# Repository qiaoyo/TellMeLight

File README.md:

# TellMeLight

TellMeLight is a USB-connected AI hardware design for visualizing local AI sessions as a persistent six-slot light queue.

Current milestone: local software simulation plus a Rev A KiCad hardware baseline. No physical PCB or USB device is required yet.

## Local Commands

Run all tests on Windows:

```powershell
powershell -ExecutionPolicy Bypass -File tools/run-node.ps1 --test host/test/*.test.js
```

Start the local Host Bridge:

```powershell
powershell -ExecutionPolicy Bypass -File tools/run-node.ps1 host/src/server-cli.js
```

Send a repeatable demo event sequence while the Host Bridge is running:

```powershell
powershell -ExecutionPolicy Bypass -File tools/run-node.ps1 host/src/demo-client.js
```

Send individual adapter-style events:

```powershell
powershell -ExecutionPolicy Bypass -File tools/run-node.ps1 host/src/event-cli.js started --id codex-1 --source codex --title "Implement firmware"
powershell -ExecutionPolicy Bypass -File tools/run-node.ps1 host/src/event-cli.js approval --id codex-1 --source codex
powershell -ExecutionPolicy Bypass -File tools/run-node.ps1 host/src/event-cli.js done --id codex-1 --source codex
```

Wrap a local command as a TellMeLight session:

```powershell
$node = powershell -ExecutionPolicy Bypass -File tools/run-node.ps1 -Eval "console.log(process.execPath)"
& $node host/src/process-cli.js --source codex --id codex-1 --title "Codex run" -- codex --help
& $node host/src/process-cli.js --source smoke --id process-smoke -- powershell -NoProfile -Command "exit 0"
```

Run a real Windows Codex request as a TellMeLight session:

```powershell
$env:TELLMELIGHT_CODEX_PROXY = "http://127.0.0.1:7892"
$node = powershell -ExecutionPolicy Bypass -File tools/run-node.ps1 -Eval "console.log(process.execPath)"
& $node host/src/codex-cli.js exec -C . --sandbox read-only "Reply with exactly: TellMeLight codex smoke ok"
& $node host/src/codex-cli.js resume --last "Continue the previous TellMeLight test"
```

The package script for the same adapter is `tml-codex`.

Open the static simulator:

```text
simulator/index.html
```

Generate the Rev A KiCad hardware baseline:

```powershell
node tools/hardware/generate-rev-a-kicad.mjs
```

Generate the Rev A1 JLC-oriented hardware baseline:

```powershell
powershell -ExecutionPolicy Bypass -File tools/run-node.ps1 tools/hardware/generate-rev-a1-kicad.mjs
```

Generate the Rev A2 pinout/JLC order package and KiCad baseline:

```powershell
powershell -ExecutionPolicy Bypass -File tools/run-node.ps1 tools/hardware/generate-rev-a2-order-package.mjs
powershell -ExecutionPolicy Bypass -File tools/run-node.ps1 tools/hardware/generate-rev-a2-kicad.mjs
powershell -ExecutionPolicy Bypass -File tools/run-node.ps1 tools/hardware/package-rev-a2-jlc.mjs
powershell -ExecutionPolicy Bypass -File tools/run-node.ps1 tools/hardware/generate-rev-a2-preview.mjs
```

The Rev A2 JLC quote/review bundle is generated at `hardware/outputs/rev_a2/jlc_upload/`.
Use `tellmelight_rev_a2_jlc_gerber_drill.zip` for PCB quote upload practice and
`tellmelight_rev_a2_jlc_assembly_bom_cpl.zip` for SMT BOM/CPL matching practice. The bundle is
explicitly `NOT_FOR_ORDER` until the JLC orientation preview is manually checked.
The static Rev A2 hardware preview is `hardware/outputs/rev_a2/preview.html`.

Generate the Rev A3 machine-readable pin-level netlist:

```powershell
powershell -ExecutionPolicy Bypass -File tools/run-node.ps1 tools/hardware/generate-rev-a3-pin-netlist.mjs
powershell -ExecutionPolicy Bypass -File tools/run-node.ps1 tools/hardware/generate-rev-a3-symbols.mjs
powershell -ExecutionPolicy Bypass -File tools/run-node.ps1 tools/hardware/lint-rev-a3-netlist.mjs
```

The Rev A3 netlist foundation lives at `hardware/netlists/rev_a3_pin_netlist.json`,
`hardware/netlists/rev_a3_pin_netlist.csv`, and
`hardware/notes/rev-a3-pin-level-schematic-feasibility.md`.
The Rev A3 local KiCad symbols live at `hardware/kicad/tellmelight_rev_a3/tellmelight_rev_a3.kicad_sym`
with a symbol-upgrade validation log at `hardware/outputs/rev_a3/symbol-upgrade-check.log`.
The Rev A3 netlist lint report lives at `hardware/outputs/rev_a3/netlist-lint.json` and
`hardware/notes/rev-a3-netlist-lint.md`.
The Rev A3 protection decisions and tonight's JLC checklist live at
`hardware/notes/rev-a3-protection-decisions.md` and
`hardware/notes/rev-a3-jlc-tonight-checklist.md`.
Generate the Rev A3 JLC preflight assembly package:

```powershell
powershell -ExecutionPolicy Bypass -File tools/run-node.ps1 tools/hardware/generate-rev-a3-jlc-preflight.mjs
```

The Rev A3 preflight package lives at `hardware/outputs/rev_a3/jlc_preflight/`.
It combines the Rev A2 assembly BOM/CPL with the Rev A3 protection additions for
JLC part matching and rough cost discovery, but it is still `PREFLIGHT_NOT_FOR_ORDER`
until the real Rev A3 PCB/Gerber/CPL exists.

Check the Rev A5 budget EVT cart before buying first-demo hardware:

```powershell
powershell -ExecutionPolicy Bypass -File tools/run-node.ps1 tools/hardware/check-rev-a5-budget.mjs
```

Flash and smoke-test the Rev A5 module firmware after the XIAO RP2040 and 6x10 matrix arrive:

```powershell
powershell -ExecutionPolicy Bypass -File tools/rev_a5/send-serial-state.ps1 -Port COM7 -States running,approval,done,error,idle,running -Brightness 0.12
```

Replace `COM7` with the actual Windows serial port.

Generate the current Rev A5 serial frame from a running Host Bridge:

```powershell
powershell -ExecutionPolicy Bypass -File tools/run-node.ps1 host/src/rev-a5-frame-cli.js --brightness 0.12
```

Open the Rev A5 budget preview:

```text
hardware/outputs/rev_a5_budget/preview.html
```

Run KiCad CLI checks with the installed Windows KiCad 10.0 path:

```powershell
& E:\kicad\bin\kicad-cli.exe sch erc --format json -o hardware/outputs/rev_a/erc.json hardware/kicad/tellmelight_rev_a/tellmelight_rev_a.kicad_sch
& E:\kicad\bin\kicad-cli.exe pcb drc --format json -o hardware/outputs/rev_a/drc.json hardware/kicad/tellmelight_rev_a/tellmelight_rev_a.kicad_pcb
& E:\kicad\bin\kicad-cli.exe sch erc --format json -o hardware/outputs/rev_a1/erc.json hardware/kicad/tellmelight_rev_a1/tellmelight_rev_a1.kicad_sch
& E:\kicad\bin\kicad-cli.exe pcb drc --format json -o hardware/outputs/rev_a1/drc.json hardware/kicad/tellmelight_rev_a1/tellmelight_rev_a1.kicad_pcb
& E:\kicad\bin\kicad-cli.exe sch erc --format json -o hardware/outputs/rev_a2/erc.json hardware/kicad/tellmelight_rev_a2/tellmelight_rev_a2.kicad_sch
& E:\kicad\bin\kicad-cli.exe pcb drc --format json -o hardware/outputs/rev_a2/drc.json hardware/kicad/tellmelight_rev_a2/tellmelight_rev_a2.kicad_pcb
```

## Simulator Interaction

- Click any of the six light slots to select it.
- Use `Set Running`, `Set Approval`, `Set Done`, or `Set Error` to update the selected session.
- Use `Clear Selected` to remove the selected visible session and compact later sessions left.
- `Add Running` appends a new running session on the newest/rightmost side.

## Milestone 1 Contents

- FIFO session model.
- Local API event schema.
- HID display frame encoder.
- Browser simulator.
- Hardware architecture notes.
- Generic process wrapper adapter.
- Direct Windows Codex JSON session adapter.
- Rev A KiCad hardware baseline with BOM, PCB floorplan, and power-budget simulation.
- Rev A1 JLC-oriented KiCad baseline with 4-layer PCB, JLC sourcing table, pogo/debug pads, and manufacturing readiness notes.
- Rev A2 pin-level review package with JLC BOM/CPL drafts, corrected USB ESD footprint direction, local TUOZHAN RGB LED footprint mapping, and circuit explanation notes.
- Rev A2 JLC upload review bundle with Gerber/drill zip, BOM/CPL zip, checksum manifest, and ordering blockers kept beside the quote files.
- Rev A2 static hardware preview page linking renders, JLC upload bundle, and Rev A3 readiness artifacts.
- Rev A3 machine-readable pin-level netlist foundation for the next real KiCad schematic draft.
- Rev A3 local KiCad symbol library for LP5024RSMR and the exact TUOZHAN S4-3528RGBTA-A RGB LED.
- Rev A3 netlist lint that checks required nets, expected single-pin review nets, and the VLED source-model review item before schematic generation.
- Rev A3 protection update with VLED TVS, explicit VBUS-to-VLED source link, USB-C shell `1M // 10nF` RC grounding, and a JLC checklist for quote/matcher validation.
- Rev A3 JLC preflight assembly package for checking the full Rev A2 BOM plus U6/R9/C17/R10 protection additions before the final Rev A3 PCB/Gerber/CPL package.
- Rev A5 budget EVT plan that stops the Rev A4 paid PCBA path and switches the first physical demo to a XIAO RP2040 plus 6x10 WS2812 matrix under an RMB 300 hard cost gate.
- Rev A5 static preview page for the budget gate, module architecture, and diffuser/mask stack.

## Out Of Scope For Milestone 1

- Real USB HID writer.
- Firmware build.
- Fabrication-ready schematic signoff, final routing, enclosure CAD, and optical validation.
- Rev A5 custom PCBA, glass, battery, and integrated enclosure tooling.
- Tool-specific log parsers for Codex, Claude, Cursor, or other AI tools.

## Design Docs

- `docs/superpowers/specs/2026-05-29-tellmelight-design.md`
- `docs/superpowers/specs/2026-05-30-rev-a-kicad-hardware-design.md`
- `docs/superpowers/specs/2026-05-30-rev-a1-jlc-fabrication-candidate-design.md`
- `docs/superpowers/specs/2026-05-30-rev-a2-pinout-jlc-order-package-design.md`
- `docs/superpowers/specs/2026-06-02-rev-a5-budget-evt-design.md`
- `docs/superpowers/specs/2026-05-29-adapter-foundation-design.md`
- `docs/adapters/contract.md`
- `docs/superpowers/brainstorm/2026-05-29-tellmelight-progress.md`
- `docs/superpowers/plans/2026-05-29-local-simulation-foundation.md`
- `docs/superpowers/plans/2026-05-30-rev-a-kicad-hardware.md`
- `docs/superpowers/plans/2026-05-30-rev-a1-jlc-fabrication-candidate.md`
- `docs/superpowers/plans/2026-05-30-rev-a2-pinout-jlc-order-package.md`
- `docs/superpowers/plans/2026-05-30-rev-a3-pin-level-schematic.md`
- `docs/superpowers/plans/2026-06-02-rev-a5-budget-evt.md`

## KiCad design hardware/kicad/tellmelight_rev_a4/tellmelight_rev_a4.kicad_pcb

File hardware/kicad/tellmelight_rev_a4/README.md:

# TellMeLight Rev A4 KiCad Project

Generated: 2026-05-31

## Contents

- `tellmelight_rev_a4.kicad_pro`: KiCad project.
- `tellmelight_rev_a4.kicad_sch`: Rev A4 review schematic/net plan inherited from Rev A2 and marked for A4.
- `tellmelight_rev_a4.kicad_sym`: TellMeLight Rev A4 local symbols for LP5024 and the TUOZHAN RGB LED, created in the Rev A4 symbol checkpoint.
- `tellmelight_rev_a4_review.kicad_sym`: Rev A4 generic review symbols for the inherited block-level schematic.
- `tellmelight_rev_a4.kicad_pcb`: 76 mm x 56 mm 4-layer routing candidate.
- `tellmelight_rev_a4.pretty/`: local TUOZHAN RGB LED footprint.

## Rev A4 Changes From Rev A2

- Board outline is reduced from 96 mm x 74 mm to 76 mm x 56 mm.
- U6 `TPD1E05U06DPY` adds VLED-to-GND TVS/ESD protection.
- R10 `0R` explicitly ties VBUS to VLED.
- R9 `1M` and C17 `10nF` implement the USB-C shell-to-GND RC network.
- C18 `1uF` adds the required RP2040 VREG_VOUT local capacitor.
- Top silkscreen includes a small A1-style separated avatar watermark in an empty optical-face area.
- Top silkscreen title includes the persistent `By Joey.qiao` attribution.
- The JLC package is a preview candidate; payment is blocked until JLC DFM and orientation preview are checked.

## Important Boundary

Rev A4 is a compact routing candidate and JLC preview package for board size, SMT matching, placement, orientation, and silkscreen review. It uses the JLC free ordinary via target: 0.45 mm outer / 0.30 mm drill. It is not a paid-order release until JLC DFM accepts the process and the user checks the SMT orientation preview.

## Visual Mapping

- D1 and D2: left long bar, oldest side.
- D3: left middle short bar.
- D4: right middle short bar.
- D5 and D6: right long bar, newest side.
- The A1-style separated avatar watermark sits near the upper top-side empty area and avoids SMT pads.

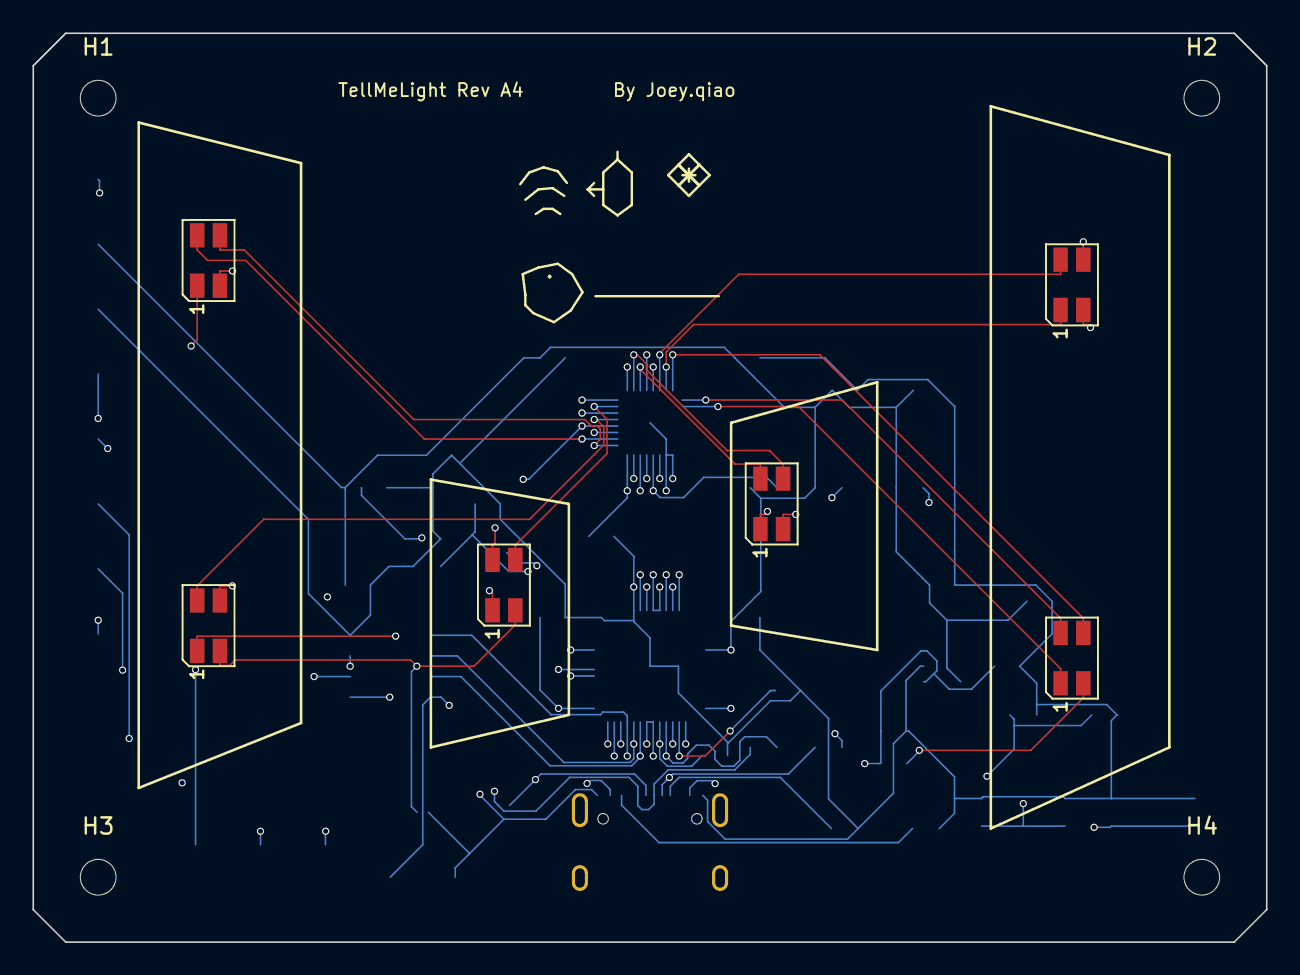
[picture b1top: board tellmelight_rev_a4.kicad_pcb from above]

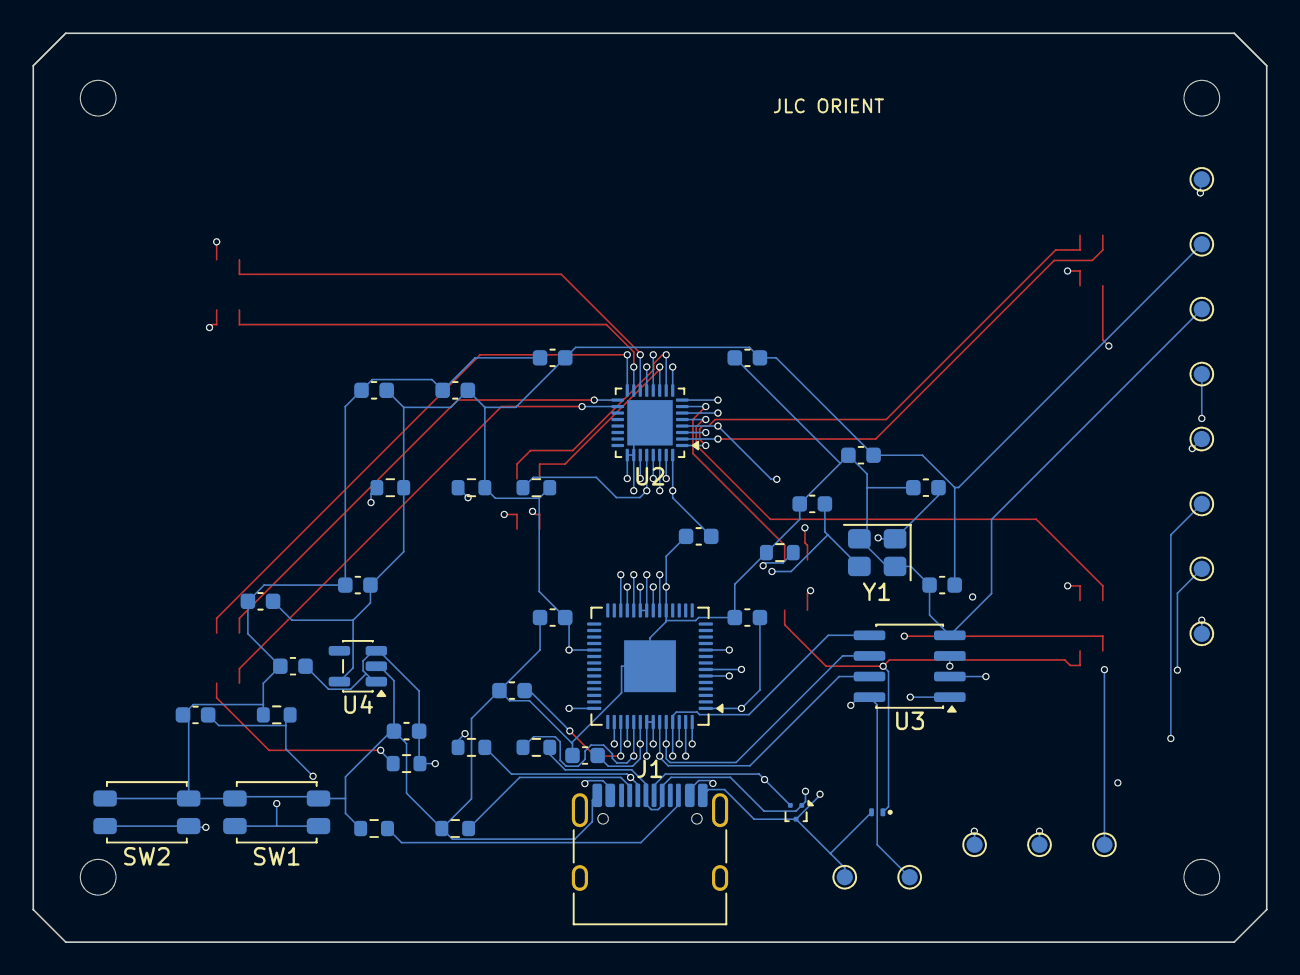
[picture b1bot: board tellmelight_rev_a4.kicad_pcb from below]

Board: 4 copper layers, 76.0 x 56.0 mm, 61 parts (51 on the bottom side), 47 nets.

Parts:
C1, C2, C3, C4, C5, C6, C7, C8, C9, C10: 100nF; C_0603_1608Metric
C11, C12: 10uF; C_0603_1608Metric
C13, C14: 33pF; C_0603_1608Metric
C15: 1uF VCAP; C_0603_1608Metric
C16: 1uF VCC; C_0603_1608Metric
C17: 10nF SHIELD; C_0603_1608Metric
C18: 1uF VREG_OUT; C_0603_1608Metric
D1, D2, D3, D4, D5, D6: S4-3528RGBTA-A; LED_RGB_TUOZHAN_S4-3528RGBTA-A_3.5x2.8mm
H1, H2, H3, H4: M2; MountingHole_2.2mm_M2
J1: USB_C; USB_C_Receptacle_HRO_TYPE-C-31-M-12
R1, R2: 27R; R_0603_1608Metric
R3, R4: 5.1k; R_0603_1608Metric
R5, R6: 4.7k; R_0603_1608Metric
R7: 10k IREF; R_0603_1608Metric
R8: 10k EN; R_0603_1608Metric
R9: 1M SHIELD; R_0603_1608Metric
R10: 0R VLED; R_0603_1608Metric
SW1: BOOT; SW_SPST_EVQP2_ShortPushTravel_H2.1mm
SW2: RESET; SW_SPST_EVQP2_ShortPushTravel_H2.1mm
TP1: VBUS; TestPoint_Pad_D1.0mm
TP2: 3V3; TestPoint_Pad_D1.0mm
TP3: GND; TestPoint_Pad_D1.0mm
TP4: SDA; TestPoint_Pad_D1.0mm
TP5: SCL; TestPoint_Pad_D1.0mm
TP6: D+; TestPoint_Pad_D1.0mm
TP7: D-; TestPoint_Pad_D1.0mm
TP8: RUN; TestPoint_Pad_D1.0mm
TP9: TP_SWDIO; TestPoint_Pad_D1.0mm
TP10: TP_SWCLK; TestPoint_Pad_D1.0mm
TP11: TP_RUN; TestPoint_Pad_D1.0mm
TP12: TP_3V3; TestPoint_Pad_D1.0mm
TP13: TP_GND; TestPoint_Pad_D1.0mm
U1: RP2040; QFN-56-1EP_7x7mm_P0.4mm_EP3.2x3.2mm
U2: LP5024; VQFN-32-1EP_4x4mm_P0.4mm_EP2.8x2.8mm
U3: W25Q32JVSS; SOIC-8_3.9x4.9mm_P1.27mm
U4: AP2112K-3.3; SOT-23-5
U5: TPD2EUSB30; Texas_DRT-3
U6: TPD1E05U06DPY; Texas_DPY0002A_0.6x1mm_P0.65mm
Y1: 12MHz; Crystal_SMD_TXC_7M-4Pin_3.2x2.5mm

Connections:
3V3: C1.1, C2.1, C3.1, C4.1, C5.1, C6.1, C9.1, C10.1, C12.1, C16.1, R5.1, R6.1, R8.1, TP2.1, TP12.1, U1.1, U1.10, U1.22, U1.23, U1.33, U1.42, U1.44, U1.49, U1.50, U2.27, U3.8, U4.5
3V3_USB: C7.1, U1.48
CC1: J1.A5, R3.1
CC2: J1.B5, R4.1
D1_B: D1.1, U2.3
D1_G: D1.3, U2.2
D1_R: D1.4, U2.1
D2_B: D2.1, U2.6
D2_G: D2.3, U2.5
D2_R: D2.4, U2.4
D3_B: D3.1, U2.9
D3_G: D3.3, U2.8
D3_R: D3.4, U2.7
D4_B: D4.1, U2.12
D4_G: D4.3, U2.11
D4_R: D4.4, U2.10
D5_B: D5.1, U2.15
D5_G: D5.3, U2.14
D5_R: D5.4, U2.13
D6_B: D6.1, U2.18
D6_G: D6.3, U2.17
D6_R: D6.4, U2.16
FLASH_CS_N_BOOTSEL: SW1.1, U1.56, U3.1
FLASH_HOLD_IO3: U1.51, U3.7
FLASH_IO0_MOSI: U1.53, U3.5
FLASH_IO1_MISO: U1.55, U3.2
FLASH_SCLK: U1.52, U3.6
FLASH_WP_IO2: U1.54, U3.3
GND: C1.2, C2.2, C3.2, C4.2, C5.2, C6.2, C7.2, C8.2, C9.2, C10.2, C11.2, C12.2, C13.2, C14.2, C15.2, C16.2, C17.2, C18.2, J1.A1, J1.A12, J1.B1, J1.B12, R3.2, R4.2, R7.2, R9.2, SW1.2, SW2.2, TP3.1, TP13.1, U1.19, U1.57, U2.25, U2.26, U2.33, U3.4, U4.2, U5.3, U6.2, Y1.2, Y1.4
I2C0_SCL: R6.2, TP5.1, U1.7, U2.29
I2C0_SDA: R5.2, TP4.1, U1.6, U2.28
LP_EN: R8.2, U2.30
LP_IREF: R7.1, U2.31
LP_VCAP: C15.1, U2.32
RP2040_VREG_OUT: C18.1, U1.45
RUN_RESET: SW2.1, TP8.1, TP11.1, U1.26
SHIELD: C17.1, J1.SH, R9.1
SWCLK: TP10.1, U1.24
SWDIO: TP9.1, U1.25
USB_DM_CONN: J1.A7, J1.B7, R2.1, TP7.1, U5.2
USB_DM_MCU: R2.2, U1.46
USB_DP_CONN: J1.A6, J1.B6, R1.1, TP6.1, U5.1
USB_DP_MCU: R1.2, U1.47
VBUS: C8.1, C11.1, J1.A4, J1.A9, J1.B4, J1.B9, R10.1, TP1.1, U4.1, U4.3
VLED: D1.2, D2.2, D3.2, D4.2, D5.2, D6.2, R10.2, U6.1
XIN: C13.1, U1.20, Y1.1
XOUT: C14.1, U1.21, Y1.3

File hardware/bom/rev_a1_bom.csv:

Designator,Qty,Kind,Value,Footprint,Preferred Part,JLC Candidate,Assembly Side,Notes,Status
U1,1,MCU,RP2040,Package_DFN_QFN:QFN-56-1EP_7x7mm_P0.4mm_EP3.2x3.2mm_ThermalVias,Raspberry Pi RP2040,C2040,Bottom,USB device controller; QFN-56 7x7 mm,review
U2,1,LED_DRIVER,LP5024RSMR,Package_DFN_QFN:VQFN-32-1EP_4x4mm_P0.4mm_EP2.8x2.8mm_ThermalVias,TI LP5024RSMR,C427525,Bottom,24-channel I2C RGB LED driver; 18 channels used,review
U3,1,FLASH,W25Q32JVSSIQ,Package_SO:SOIC-8_3.9x4.9mm_P1.27mm,Winbond W25Q32JVSSIQ,C82344,Bottom,QSPI flash for RP2040 firmware,review
U4,1,LDO,AP2112K-3.3TRG1,Package_TO_SOT_SMD:SOT-23-5,Diodes Inc AP2112K-3.3TRG1,C51118,Bottom,3V3 regulator from USB VBUS,review
U5,1,USB_ESD,TPD2EUSB30DRTR,Package_TO_SOT_SMD:SOT-23-6,TI TPD2EUSB30DRTR,C94934,Bottom,USB D+/D- ESD protection near J1,review
J1,1,USB_C,USB_C_Receptacle_USB2.0,Connector_USB:USB_C_Receptacle_HRO_TYPE-C-31-M-12,HRO TYPE-C-31-M-12,C165948,Bottom,USB-C power and full-speed data,review
"TP_SWDIO,TP_SWCLK,TP_RUN,TP_3V3,TP_GND",5,DEBUG,Pogo test pads,TestPoint:TestPoint_Pad_D1.0mm,Generic 1.0 mm SMT test pad,JLC basic mechanical,Bottom,"SWDIO, SWCLK, RUN, 3V3, GND without a through-hole header",review
"SW1,SW2",2,SWITCH,BOOT_RESET,Button_Switch_SMD:SW_SPST_EVQP2_ShortPushTravel_H2.1mm,Panasonic EVQP2-class,JLC matched switch,Bottom,BOOTSEL and reset service buttons on back,review
Y1,1,CRYSTAL,12MHz,Crystal:Crystal_SMD_TXC_7M-4Pin_3.2x2.5mm,12 MHz 3.2x2.5 mm crystal,JLC matched crystal,Bottom,RP2040 clock source; validate load caps with selected crystal,review
D1-D6,6,RGB_LED,S4-3528RGBTA-A,LED_SMD:LED_RGB_Wuerth-PLCC4_3.2x2.8mm_150141M173100,OPSCO S4-3528RGBTA-A,C2827321,Top,Common-anode RGB emitters under diffuser bars,review
"R1,R2",2,RESISTOR,27R,Resistor_SMD:R_0603_1608Metric,1% 0603 resistor,JLC basic 0603,Bottom,USB D+/D- series resistors,review
"R3,R4",2,RESISTOR,5.1k,Resistor_SMD:R_0603_1608Metric,1% 0603 resistor,JLC basic 0603,Bottom,USB-C CC pull-downs,review
"R5,R6",2,RESISTOR,4.7k,Resistor_SMD:R_0603_1608Metric,1% 0603 resistor,JLC basic 0603,Bottom,I2C pull-ups to 3V3,review
C1-C10,10,CAPACITOR,100nF,Capacitor_SMD:C_0603_1608Metric,X7R 0603 capacitor,JLC basic 0603,Bottom,Local IC decoupling,review
"C11,C12",2,CAPACITOR,10uF,Capacitor_SMD:C_0603_1608Metric,X5R/X7R 0603 or 0805 capacitor,JLC basic/common,Bottom,LDO input/output and LED rail bulk,review
"C13,C14",2,CAPACITOR,Crystal load,Capacitor_SMD:C_0603_1608Metric,Load capacitor matched to selected crystal,JLC matched capacitor,Bottom,RP2040 crystal load caps,review
TP1-TP8,8,TESTPOINT,1.0mm pad,TestPoint:TestPoint_Pad_D1.0mm,Generic 1.0 mm SMT test pad,JLC basic mechanical,Bottom,"VBUS, 3V3, GND, I2C, USB, RUN bring-up points",review
H1-H4,4,MECHANICAL,M2 mounting hole,MountingHole:MountingHole_2.2mm_M2,Generic M2 clearance,Not assembled,Mechanical,Optional enclosure/diffuser fastening,review

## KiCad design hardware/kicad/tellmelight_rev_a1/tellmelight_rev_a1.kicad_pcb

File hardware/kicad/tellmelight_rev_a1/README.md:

# TellMeLight Rev A1 KiCad Project

Generated: 2026-05-30

## Contents

- `tellmelight_rev_a1.kicad_pro`: KiCad project.
- `tellmelight_rev_a1.kicad_sch`: block-level schematic/net plan for Rev A1.
- `tellmelight_rev_a1.kicad_sym` and `sym-lib-table`: local symbols so KiCad can export a review BOM.
- `tellmelight_rev_a1.kicad_pcb`: 4-layer PCB floorplan with stock KiCad footprints.

## Important Boundary

This is a Rev A1 JLC-oriented CAD baseline for review. It is not a fabrication release until the pin-by-pin schematic, routing, footprint models, JLC BOM matching, and DFM are reviewed.

## Manufacturing Direction

- 4-layer PCB.
- Double-sided SMT assembly.
- No assumed user hand-soldering.
- Pogo/test pads replace the visible SWD header direction.
- Front side is kept mostly optical; back side carries logic, USB, power, and service controls.

## Visual Mapping

- D1 and D2: left long bar, oldest side.
- D3: left middle short bar.
- D4: right middle short bar.
- D5 and D6: right long bar, newest side.

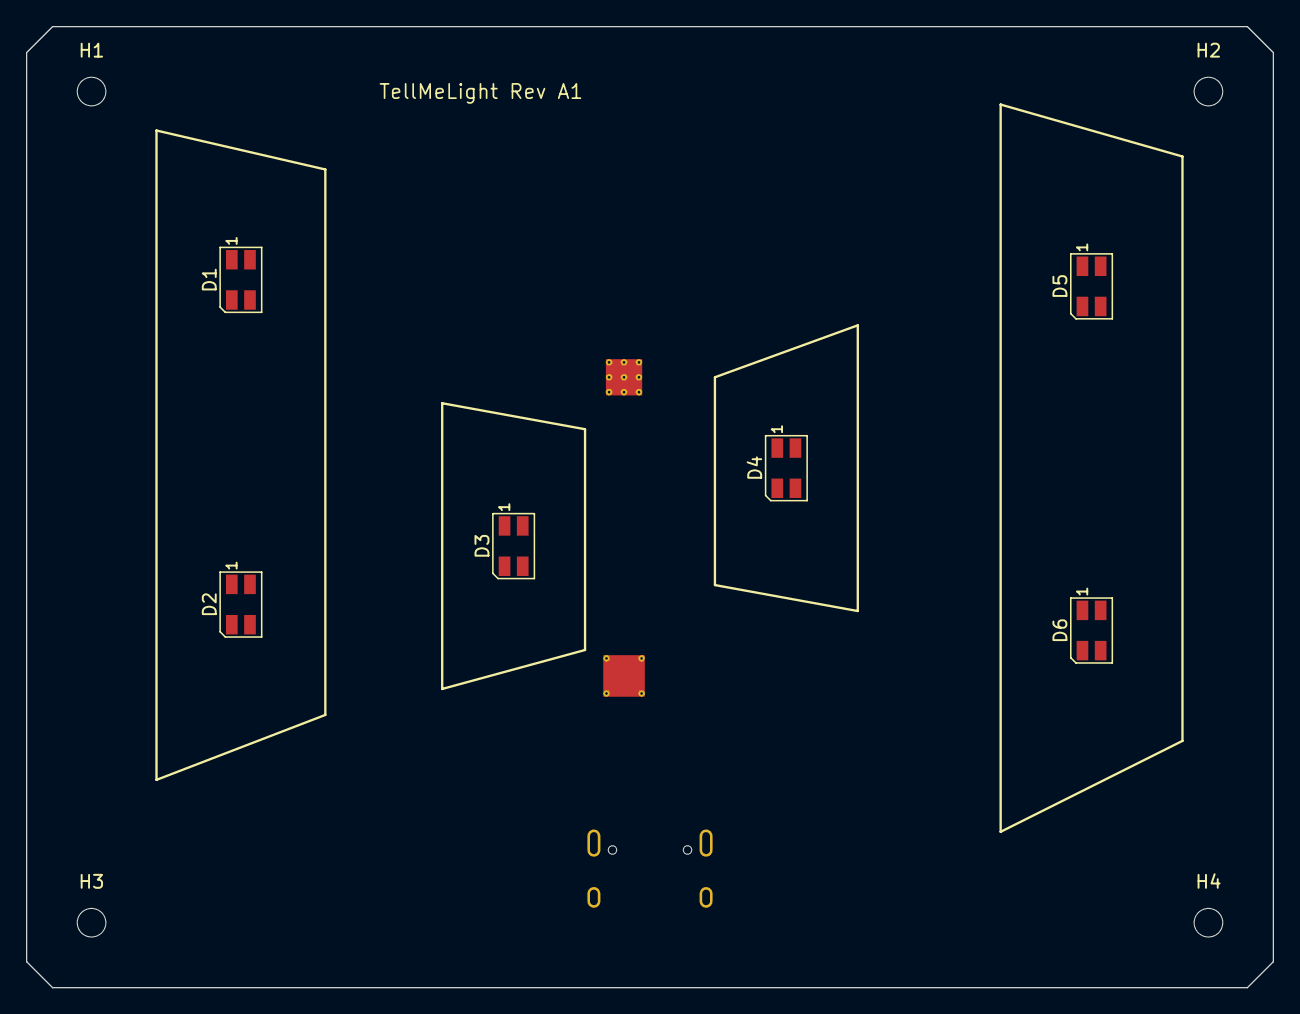
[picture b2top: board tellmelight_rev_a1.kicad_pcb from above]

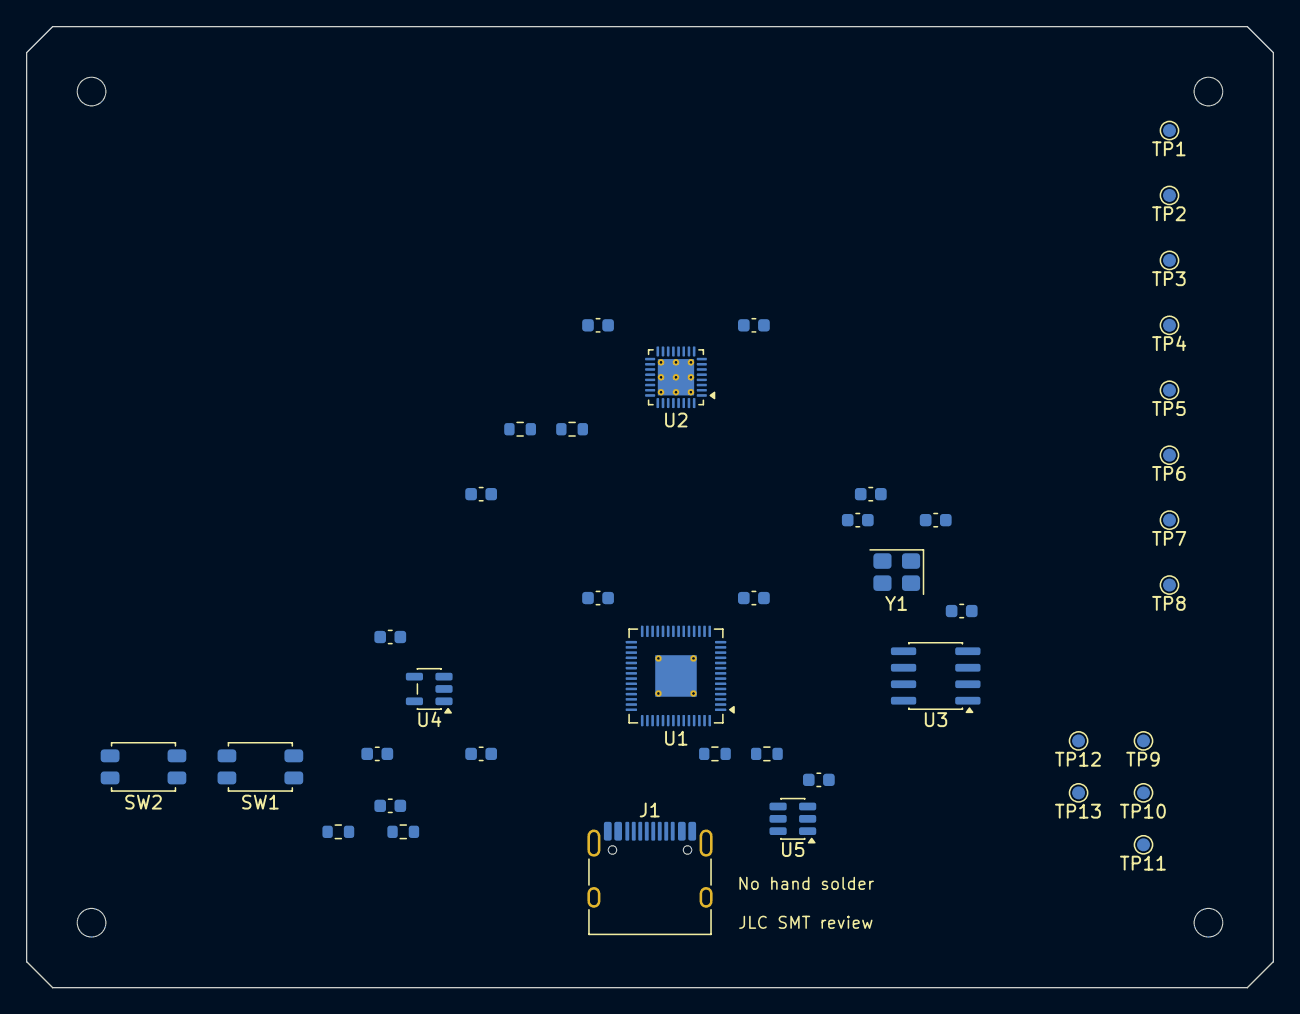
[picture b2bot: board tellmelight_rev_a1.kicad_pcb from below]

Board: 4 copper layers, 96.0 x 74.0 mm, 52 parts (42 on the bottom side), 4 nets, no tracks yet.

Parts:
C1, C2, C3, C4, C5, C6, C7, C8, C9, C10: 100nF; C_0603_1608Metric
C11, C12: 10uF; C_0603_1608Metric
C13, C14: CL; C_0603_1608Metric
D1, D2, D3, D4, D5, D6: S4-3528RGBTA-A; LED_RGB_Wuerth-PLCC4_3.2x2.8mm_150141M173100
H1, H2, H3, H4: M2; MountingHole_2.2mm_M2
J1: USB_C; USB_C_Receptacle_HRO_TYPE-C-31-M-12
R1, R2: 27R; R_0603_1608Metric
R3, R4: 5.1k; R_0603_1608Metric
R5, R6: 4.7k; R_0603_1608Metric
SW1: BOOT; SW_SPST_EVQP2_ShortPushTravel_H2.1mm
SW2: RESET; SW_SPST_EVQP2_ShortPushTravel_H2.1mm
TP1: VBUS; TestPoint_Pad_D1.0mm
TP2: 3V3; TestPoint_Pad_D1.0mm
TP3: GND; TestPoint_Pad_D1.0mm
TP4: SDA; TestPoint_Pad_D1.0mm
TP5: SCL; TestPoint_Pad_D1.0mm
TP6: D+; TestPoint_Pad_D1.0mm
TP7: D-; TestPoint_Pad_D1.0mm
TP8: RUN; TestPoint_Pad_D1.0mm
TP9: TP_SWDIO; TestPoint_Pad_D1.0mm
TP10: TP_SWCLK; TestPoint_Pad_D1.0mm
TP11: TP_RUN; TestPoint_Pad_D1.0mm
TP12: TP_3V3; TestPoint_Pad_D1.0mm
TP13: TP_GND; TestPoint_Pad_D1.0mm
U1: RP2040; QFN-56-1EP_7x7mm_P0.4mm_EP3.2x3.2mm_ThermalVias
U2: LP5024; VQFN-32-1EP_4x4mm_P0.4mm_EP2.8x2.8mm_ThermalVias
U3: W25Q32JVSS; SOIC-8_3.9x4.9mm_P1.27mm
U4: AP2112K-3.3; SOT-23-5
U5: TPD2EUSB30; SOT-23-6
Y1: 12MHz; Crystal_SMD_TXC_7M-4Pin_3.2x2.5mm

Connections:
GND_USB_A: J1.A1, J1.B12
GND_USB_B: J1.A12, J1.B1
VBUS_USB_A: J1.A4, J1.B9
VBUS_USB_B: J1.A9, J1.B4

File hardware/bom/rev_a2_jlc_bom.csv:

Comment,Designator,Footprint,LCSC Part
RP2040,U1,Package_DFN_QFN:QFN-56-1EP_7x7mm_P0.4mm_EP3.2x3.2mm_ThermalVias,C2040
LP5024RSMR,U2,Package_DFN_QFN:VQFN-32-1EP_4x4mm_P0.4mm_EP2.8x2.8mm_ThermalVias,C427525
W25Q32JVSSIQ,U3,Package_SO:SOIC-8_3.9x4.9mm_P1.27mm,C179173
AP2112K-3.3TRG1,U4,Package_TO_SOT_SMD:SOT-23-5,C51118
TPD2EUSB30DRTR,U5,Package_TO_SOT_SMD:Texas_DRT-3,C94934
TYPE-C-31-M-12,J1,Connector_USB:USB_C_Receptacle_HRO_TYPE-C-31-M-12,C165948
S4-3528RGBTA-A,"D1,D2,D3,D4,D5,D6",TellMeLight_Rev_A2:LED_RGB_TUOZHAN_S4-3528RGBTA-A_3.5x2.8mm,C2827321
27R,"R1,R2",Resistor_SMD:R_0603_1608Metric,C25190
5.1k,"R3,R4",Resistor_SMD:R_0603_1608Metric,C23186
4.7k,"R5,R6",Resistor_SMD:R_0603_1608Metric,C23162
10k,"R7,R8",Resistor_SMD:R_0603_1608Metric,C25804
100nF,"C1,C2,C3,C4,C5,C6,C7,C8,C9,C10",Capacitor_SMD:C_0603_1608Metric,C1591
10uF,"C11,C12",Capacitor_SMD:C_0603_1608Metric,C19702
33pF,"C13,C14",Capacitor_SMD:C_0603_1608Metric,C2594250
1uF,"C15,C16",Capacitor_SMD:C_0603_1608Metric,C15849
12MHz,Y1,Crystal:Crystal_SMD_TXC_7M-4Pin_3.2x2.5mm,C9002
BOOT_RESET,"SW1,SW2",Button_Switch_SMD:SW_SPST_EVQP2_ShortPushTravel_H2.1mm,C79161

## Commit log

2026-05-28 Add TellMeLight design spec
2026-05-28 docs: add local simulation implementation plan
2026-05-28 docs: align cleared FIFO plan
2026-05-28 chore: ignore local worktrees
2026-05-28 chore: add local project skeleton
2026-05-28 feat: add FIFO session model
2026-05-28 feat: add local event schema
2026-05-28 feat: encode HID display frames
2026-05-28 docs: record local implementation progress
2026-05-28 feat: add local light simulator
2026-05-29 docs: record local simulation hardware boundary
2026-05-29 docs: describe local simulation milestone
2026-05-29 fix: validate ended outcomes
2026-05-29 feat: select simulator slots
2026-05-29 style: refine simulator light strips
2026-05-29 fix: keep right middle strip upright
2026-05-29 docs: specify host bridge milestone
2026-05-29 docs: plan host bridge milestone
2026-05-29 feat: add host bridge state
2026-05-29 feat: serve host bridge API
2026-05-29 feat: add host bridge commands
2026-05-29 feat: connect simulator to host bridge
2026-05-29 docs: record host bridge milestone
2026-05-29 docs: specify adapter foundation
2026-05-29 docs: plan adapter foundation
2026-05-29 feat: add host bridge event client
2026-05-29 feat: add adapter event CLI
2026-05-29 docs: add adapter contract
2026-05-29 docs: specify process adapter
2026-05-29 docs: plan process adapter
2026-05-29 feat: add generic process runner
2026-05-29 feat: add process adapter CLI
2026-05-29 docs: document process adapter
2026-05-29 docs: fix process wrapper examples
2026-05-30 docs: plan windows codex integration
2026-05-30 feat: map codex json events
2026-05-30 feat: add tml codex cli
2026-05-30 feat: run codex json sessions
2026-05-30 docs: document windows codex integration
2026-05-30 fix: preserve codex session titles
2026-05-30 docs: plan rev a kicad hardware
2026-05-30 feat: add rev a kicad hardware baseline
2026-05-30 docs: define rev a1 jlc hardware direction
2026-05-30 docs: plan rev a1 jlc hardware baseline
2026-05-30 feat: add rev a1 jlc hardware baseline
2026-05-30 docs: add rev a1 preview and cost estimate
2026-05-30 docs: define rev a2 pinout and jlc package
2026-05-30 docs: plan rev a2 pinout jlc package
2026-05-30 feat: add rev a2 order package
2026-05-30 feat: add rev a2 kicad baseline
2026-05-30 feat: map rev a2 rgb led footprint
2026-05-30 feat: package rev a2 jlc upload bundle
2026-05-30 feat: add rev a3 pin netlist foundation
2026-05-30 feat: add rev a3 local symbols
2026-05-30 feat: lint rev a3 pin netlist
2026-05-30 feat: add rev a2 hardware preview
2026-05-30 feat: add rev a3 protection decisions
2026-05-30 fix: correct rev a3 vled tvs jlc candidate
2026-05-30 feat: add rev a3 jlc preflight package
2026-05-30 feat: add rev a3 formal jlc review package
2026-05-30 design: refine rev a3 avatar watermark
2026-05-30 design: add rev a3 attribution silkscreen
2026-05-31 design: add rev a4 routing checkpoint
2026-05-31 hardware: finish rev a4 routing preview package
2026-05-31 hardware: correct rev a4 ordinary via routing
2026-05-31 hardware: align rev a4 with JLC free vias
2026-06-01 design: add rev a5 budget evt plan
2026-06-01 feat: add rev a5 host frame output
2026-06-01 docs: add rev a5 budget preview
